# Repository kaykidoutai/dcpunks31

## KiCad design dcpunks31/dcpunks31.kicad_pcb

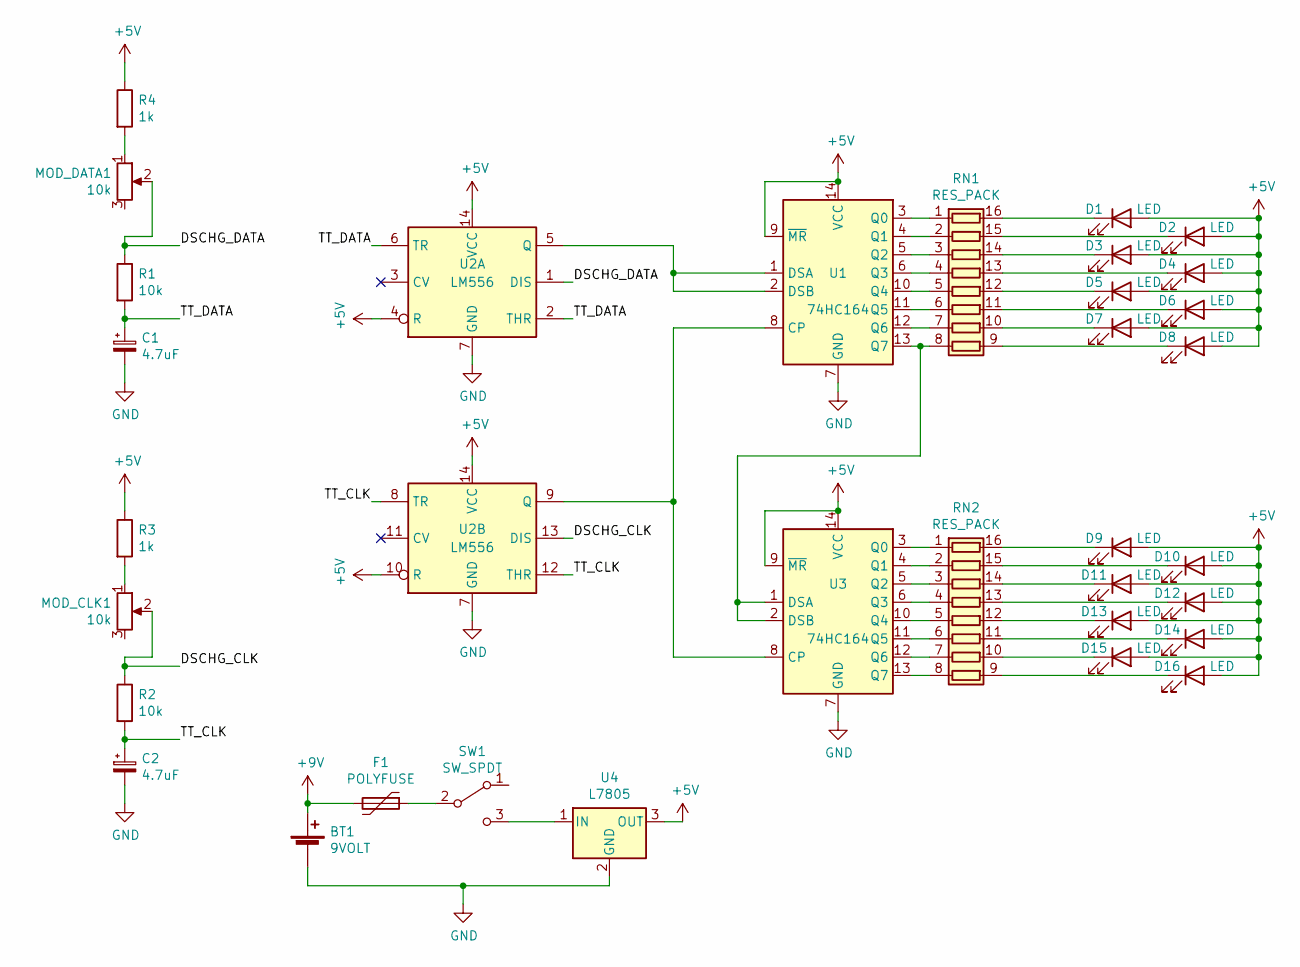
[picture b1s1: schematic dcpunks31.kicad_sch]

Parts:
BT1: 9VOLT; BAT_BH9VPC
C1, C2: 4.7uF; CP_Elec_4x5.4
D1, D2, D3, D4, D5, D6, D7, D8, D9, D10, D11, D12, D13, D14, D15, D16: LED; LED_D3.0mm
F1: POLYFUSE; Fuse_1206_3216Metric_Pad1.42x1.75mm_HandSolder
MOD_CLK1: 10k; TRIM_3306F-1-103
MOD_DATA1: 10k; TRIM_3306F-1-103
R1, R2: 10k; R_0603_1608Metric_Pad0.98x0.95mm_HandSolder
R3, R4: 1k; R_0603_1608Metric_Pad0.98x0.95mm_HandSolder
RN1, RN2: RES_PACK; R_Array_Convex_8x0602
SW1: SW_SPDT; SW_E-Switch_EG1224_SPDT_Angled
U1, U3: 74HC164; SOIC-14_3.9x8.7mm_P1.27mm
U2: LM556; SOIC-14_3.9x8.7mm_P1.27mm
U4: L7805; TO-252-2

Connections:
+5V: D1.2 (A), D2.2 (A), D3.2 (A), D4.2 (A), D5.2 (A), D6.2 (A), D7.2 (A), D8.2 (A), D9.2 (A), D10.2 (A), D11.2 (A), D12.2 (A), D13.2 (A), D14.2 (A), D15.2 (A), D16.2 (A), R3.1, R4.1, U1.9 (~MR), U1.14 (VCC), U2.4 (R), U2.10 (R), U2.14 (VCC), U3.9 (~MR), U3.14 (VCC), U4.3 (OUT)
+9V: BT1.1 (+), F1.2
/DSCHG_CLK: MOD_CLK1.2, R2.1, U2.13 (DIS)
/DSCHG_DATA: MOD_DATA1.2, R1.1, U2.1 (DIS)
/TT_CLK: C2.1, R2.2, U2.8 (TR), U2.12 (THR)
/TT_DATA: C1.1, R1.2, U2.2 (THR), U2.6 (TR)
GND: BT1.2 (-), C1.2, C2.2, U1.7 (GND), U2.7 (GND), U3.7 (GND), U4.2 (GND)
unnamed: D1.1 (K), RN1.16 (R1.2)
unnamed: D2.1 (K), RN1.15 (R2.2)
unnamed: D3.1 (K), RN1.14 (R3.2)
unnamed: D4.1 (K), RN1.13 (R4.2)
unnamed: D5.1 (K), RN1.12 (R5.2)
unnamed: D6.1 (K), RN1.11 (R6.2)
unnamed: D7.1 (K), RN1.10 (R7.2)
unnamed: D8.1 (K), RN1.9 (R8.2)
unnamed: D9.1 (K), RN2.16 (R1.2)
unnamed: D10.1 (K), RN2.15 (R2.2)
unnamed: D11.1 (K), RN2.14 (R3.2)
unnamed: D12.1 (K), RN2.13 (R4.2)
unnamed: D13.1 (K), RN2.12 (R5.2)
unnamed: D14.1 (K), RN2.11 (R6.2)
unnamed: D15.1 (K), RN2.10 (R7.2)
unnamed: D16.1 (K), RN2.9 (R8.2)
unnamed: F1.1, SW1.2 (B)
unnamed: MOD_CLK1.1, R3.2
unnamed: MOD_DATA1.1, R4.2
unnamed: RN1.1 (R1.1), U1.3 (Q0)
unnamed: RN1.2 (R2.1), U1.4 (Q1)
unnamed: RN1.3 (R3.1), U1.5 (Q2)
unnamed: RN1.4 (R4.1), U1.6 (Q3)
unnamed: RN1.5 (R5.1), U1.10 (Q4)
unnamed: RN1.6 (R6.1), U1.11 (Q5)
unnamed: RN1.7 (R7.1), U1.12 (Q6)
unnamed: RN1.8 (R8.1), U1.13 (Q7), U3.1 (DSA), U3.2 (DSB)
unnamed: RN2.1 (R1.1), U3.3 (Q0)
unnamed: RN2.2 (R2.1), U3.4 (Q1)
unnamed: RN2.3 (R3.1), U3.5 (Q2)
unnamed: RN2.4 (R4.1), U3.6 (Q3)
unnamed: RN2.5 (R5.1), U3.10 (Q4)
unnamed: RN2.6 (R6.1), U3.11 (Q5)
unnamed: RN2.7 (R7.1), U3.12 (Q6)
unnamed: RN2.8 (R8.1), U3.13 (Q7)
unnamed: SW1.3 (C), U4.1 (IN)
unnamed: U1.1 (DSA), U1.2 (DSB), U2.5 (Q)
unnamed: U1.8 (CP), U2.9 (Q), U3.8 (CP)

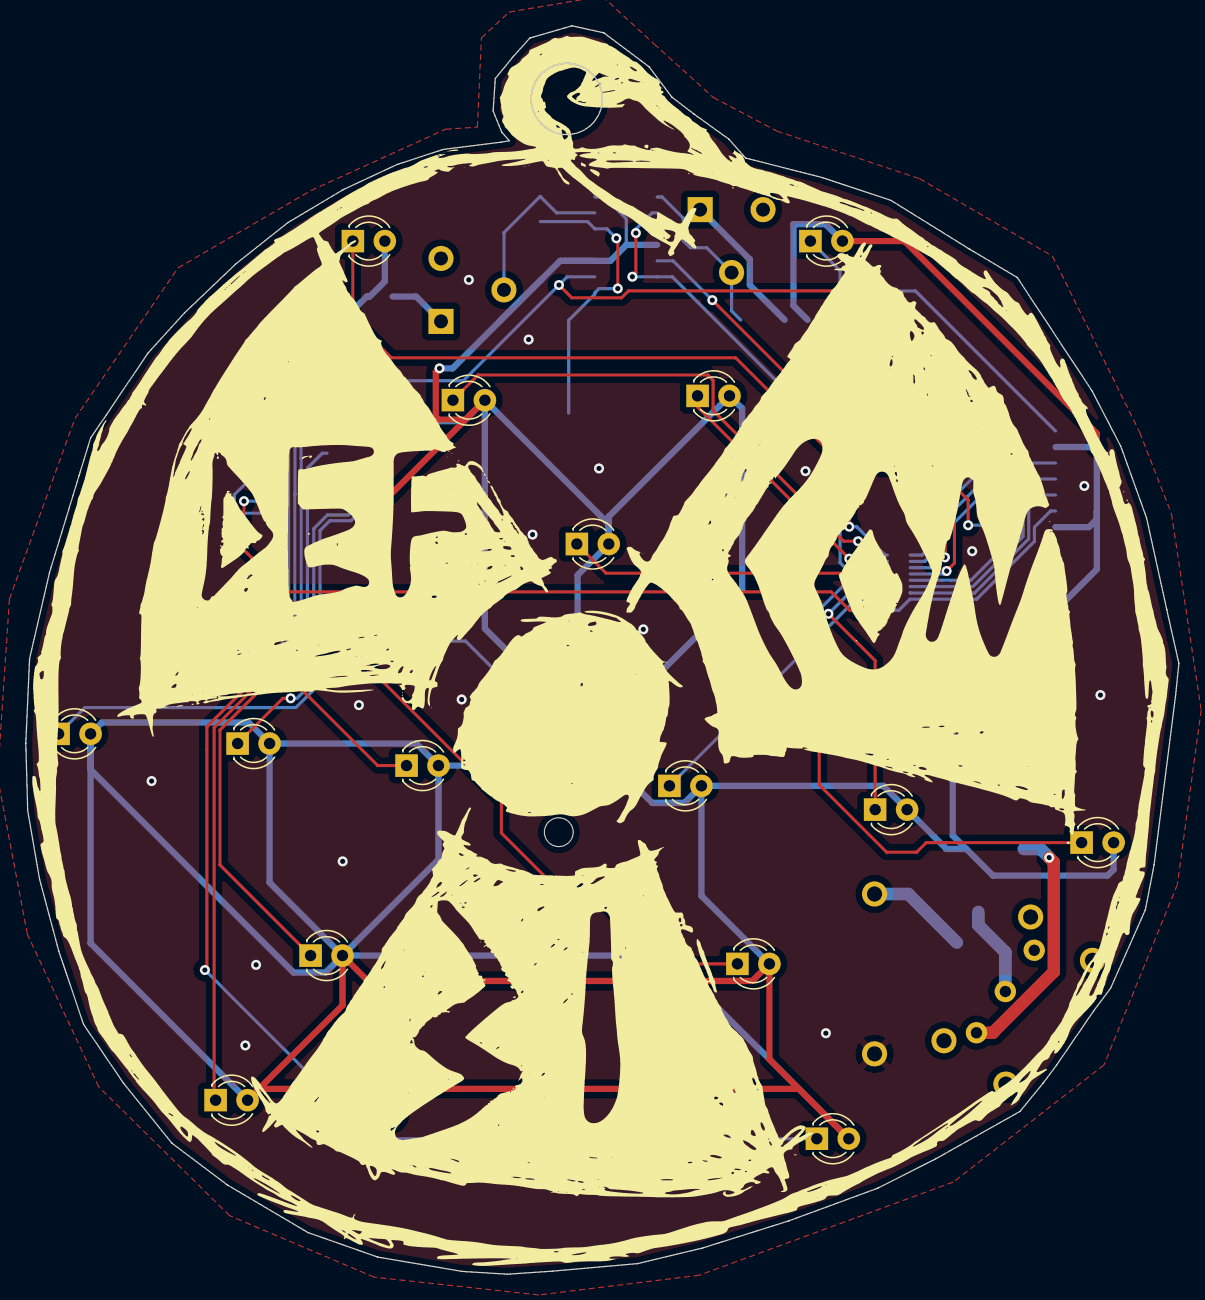
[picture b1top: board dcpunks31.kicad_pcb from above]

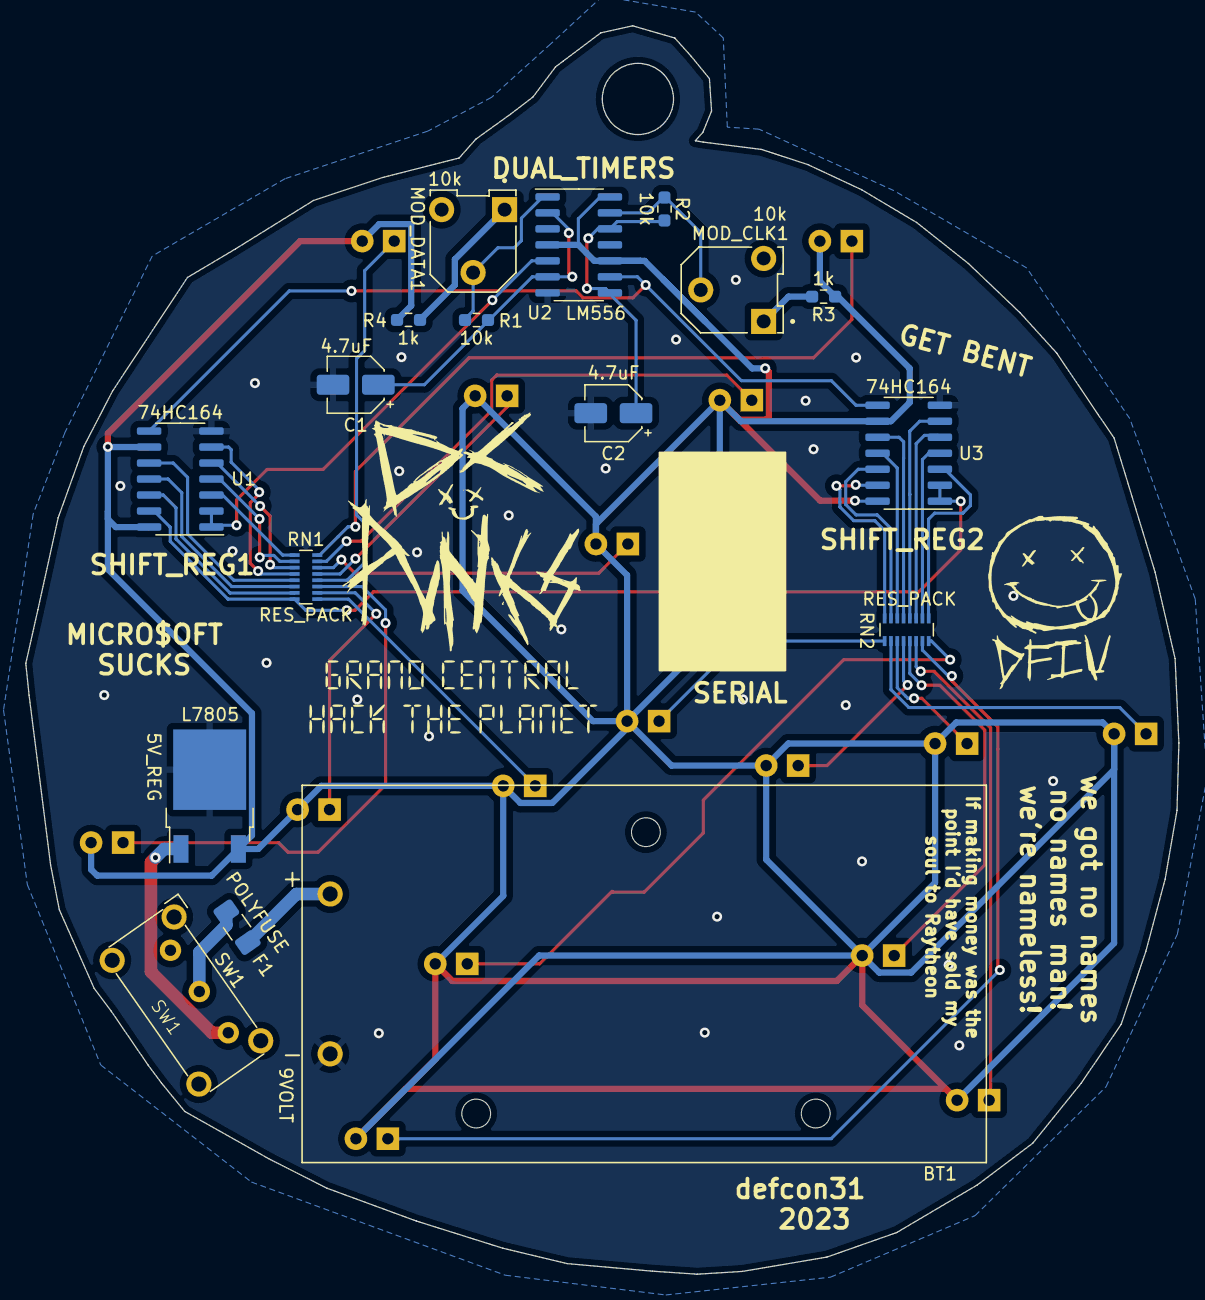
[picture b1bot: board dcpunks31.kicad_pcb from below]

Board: 2 copper layers, 91.6 x 99.2 mm, 33 parts (17 on the bottom side), 45 nets.

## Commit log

2022-10-09 OOPS
2022-10-09 moar
2022-10-23 should be ready for mass production
2022-11-09 almost done
2022-11-24 ordered
2023-07-27 did some stuff
